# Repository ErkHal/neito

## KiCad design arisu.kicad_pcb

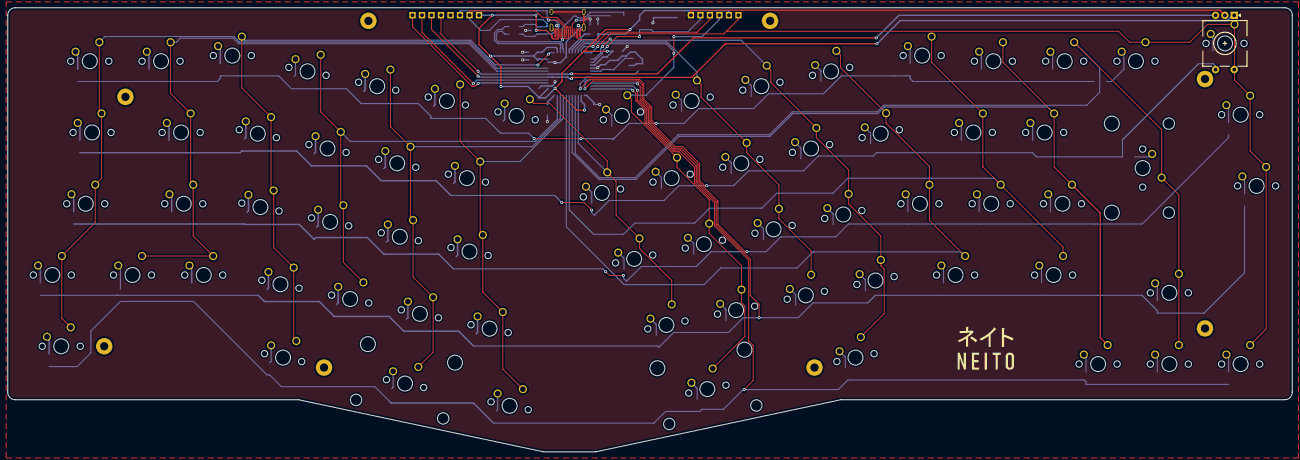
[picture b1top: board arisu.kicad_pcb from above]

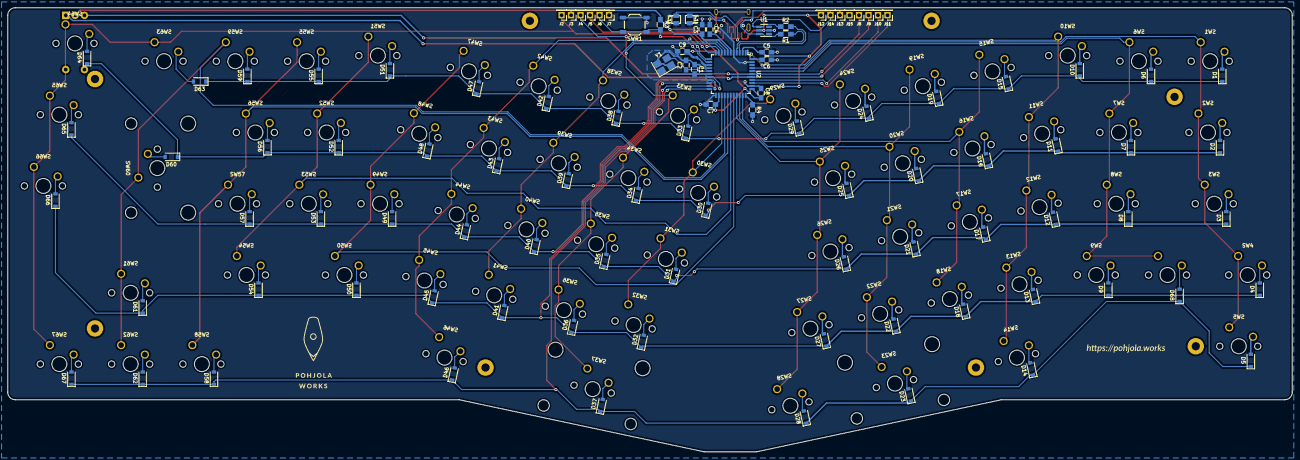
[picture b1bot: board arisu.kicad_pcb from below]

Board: 2 copper layers, 343.4 x 118.7 mm, 179 parts (101 on the bottom side), 106 nets.

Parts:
C1, C2: 22pF; C_0805_HandSoldering
C3: 10uF; C_0805_HandSoldering
C4: 1uF (±10%); C_0805_HandSoldering
C5: 1uF; C_0805_HandSoldering
C6, C7, C8, C9: 0.1uF; C_0805_HandSoldering
D1, D2, D3, D4, D5, D6, D7, D8, D9, D10, D11, D12, D13, D14, D15, D16, D17, D18, D19, D20, D21, D22, D23, D24, D25, D26, D27, D28, D29, D30, D31, D32, D33, D34, D35, D36, D37, D38, D39, D40, D41, D42, D43, D44, D45, D46, D47, D48, D49, D50, D51, D52, D53, D54, D55, D56, D57, D58, D59, D60, D61, D62, D63, D64, D65, D66, D67, D68: D; D_SOD-123
ENC0: Rotary_Encoder_Switch; RotaryEncoder_EC11
H1, H2, H3, H4, H5, H6, H7, H8: MountingHole; MountingHole_2.2mm_M2_Pad
J2: MISO; Pin_Header_Straight_1x01_Pitch2.54mm
J3, J12: VCC; Pin_Header_Straight_1x01_Pitch2.54mm
J4: SCK; Pin_Header_Straight_1x01_Pitch2.54mm
J5: MOSI; Pin_Header_Straight_1x01_Pitch2.54mm
J6: RES; Pin_Header_Straight_1x01_Pitch2.54mm
J7, J15: GND; Pin_Header_Straight_1x01_Pitch2.54mm
J8: PF4; Pin_Header_Straight_1x01_Pitch2.54mm
J9: PF5; Pin_Header_Straight_1x01_Pitch2.54mm
J10: PF6; Pin_Header_Straight_1x01_Pitch2.54mm
J11: PF7; Pin_Header_Straight_1x01_Pitch2.54mm
J13: D+; Pin_Header_Straight_1x01_Pitch2.54mm
J14: D-; Pin_Header_Straight_1x01_Pitch2.54mm
R1, R2: 22; R_0805_HandSoldering
R3, R4: 10K; R_0805_HandSoldering
R_CC1, R_CC2: 5.1k; R_2012
SW1, SW6, SW7, SW8, SW9, SW10, SW11, SW12, SW13, SW15, SW16, SW17, SW18, SW19, SW20, SW21, SW22, SW24, SW25, SW26, SW27, SW28, SW29, SW30, SW31, SW32, SW33, SW34, SW35, SW36, SW38, SW39, SW40, SW41, SW42, SW43, SW44, SW45, SW47, SW48, SW49, SW50, SW51, SW52, SW53, SW55, SW56, SW57, SW58, SW59, SW61, SW62, SW63, SW64, SW65, SW66, SW67: SW_Push; SW_Cherry_MX_1.00u_PCB
SW2, SW5, SW14, SW46: SW_Push; SW_Cherry_MX_1.50u_PCB
SW3, SW54: SW_Push; SW_Cherry_MX_1.75u_PCB
SW4: SW_Push; SW_Cherry_MX_1.25u_PCB
SW23: SW_Push; SW_Cherry_MX_2.00u_PCB_ReversedStabilizers
SW37: SW_Push; SW_Cherry_MX_2.75u_PCB_ReversedStabilizers
SW60: SW_Push; SW_Cherry_MX_2.00u_PCB
SW68: SW_Push; MX_1.00u_PCB
SWR1: SW_Push; SW_SPST_TL3342
U1: USBLC6-2SC6; SOT-23-6_Handsoldering
U2: ATmega32U4-AU; TQFP-44_10x10mm_Pitch0.8mm
USB_C1: USB_C_Receptacle_HRO_TYPE-C-31-M-12; USB_C_Receptacle_HRO_TYPE-C-31-M-12-HandSoldering
Y1: Crystal_GND24; Crystal_SMD_SeikoEpson_FA238-4pin_3.2x2.5mm_HandSoldering

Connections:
/MISO: ENC0.S2, J2.1, SW63.1, SW64.1, SW65.1, SW66.1, SW67.1, U2.11
/MOSI: J5.1, U2.10
/PF4: ENC0.B, J8.1, U2.39
/PF5: ENC0.A, J9.1, U2.38
/PF6: J10.1, U2.37
/PF7: J11.1, U2.36
/SCK: J4.1, SW33.1, SW34.1, SW35.1, SW36.1, SW37.1, U2.9
/col0: SW1.1, SW2.1, SW3.1, SW4.1, SW5.1, U2.41
/col1: SW6.1, SW7.1, SW8.1, SW9.1, SW68.1, U2.40
/col2: SW10.1, SW11.1, SW12.1, SW13.1, SW14.1, U2.1
/col3: SW15.1, SW16.1, SW17.1, SW18.1, U2.32
/col4: SW19.1, SW20.1, SW21.1, SW22.1, SW23.1, U2.31
/col5: SW24.1, SW25.1, SW26.1, SW27.1, SW28.1, U2.30
/col6: SW29.1, SW30.1, SW31.1, SW32.1, U2.25
/col8: SW38.1, SW39.1, SW40.1, SW41.1, U2.8
/col9: SW42.1, SW43.1, SW44.1, SW45.1, SW46.1, U2.12
/col10: SW47.1, SW48.1, SW49.1, SW50.1, U2.29
/col11: SW51.1, SW52.1, SW53.1, SW54.1, U2.28
/col12: SW55.1, SW56.1, SW57.1, SW58.1, U2.27
/col13: SW59.1, SW60.1, SW61.1, SW62.1, U2.26
/row0: D1.1, D6.1, D10.1, D15.1, D19.1, D24.1, D29.1, D33.1, D38.1, D42.1, D47.1, D51.1, D55.1, D59.1, D63.1, U2.18
/row1: D2.1, D7.1, D11.1, D16.1, D20.1, D25.1, D30.1, D34.1, D39.1, D43.1, D48.1, D52.1, D56.1, D60.1, D64.1, ENC0.S1, U2.19
/row2: D3.1, D8.1, D12.1, D17.1, D21.1, D26.1, D31.1, D35.1, D40.1, D44.1, D49.1, D53.1, D57.1, D65.1, U2.20
/row3: D4.1, D9.1, D13.1, D18.1, D22.1, D27.1, D32.1, D36.1, D41.1, D45.1, D50.1, D54.1, D61.1, D66.1, U2.21
/row4: D5.1, D14.1, D23.1, D28.1, D37.1, D46.1, D58.1, D62.1, D67.1, D68.1, U2.22
/~RES~: J6.1, R3.2, SWR1.2, U2.13
D+: R1.1, U2.4
D-: R2.1, U2.3
GND: C1.1, C2.2, C3.2, C4.2, C5.2, C6.2, C7.2, C8.2, C9.2, ENC0.C, J7.1, J15.1, R4.2, R_CC1.1, R_CC2.2, SWR1.1, U1.2, U2.5, U2.15, U2.23, U2.35, U2.43, USB_C1.A1, USB_C1.A12, USB_C1.S1, Y1.2, Y1.4
unnamed: C4.1, U2.6
unnamed: D1.2, SW1.2
unnamed: D2.2, SW2.2
unnamed: D3.2, SW3.2
unnamed: D4.2, SW4.2
unnamed: D5.2, SW5.2
unnamed: D6.2, SW6.2
unnamed: D7.2, SW7.2
unnamed: D8.2, SW8.2
unnamed: D9.2, SW9.2
unnamed: D10.2, SW10.2
unnamed: D11.2, SW11.2
unnamed: D12.2, SW12.2
unnamed: D13.2, SW13.2
unnamed: D14.2, SW14.2
unnamed: D15.2, SW15.2
unnamed: D16.2, SW16.2
unnamed: D17.2, SW17.2
unnamed: D18.2, SW18.2
unnamed: D19.2, SW19.2
unnamed: D20.2, SW20.2
unnamed: D21.2, SW21.2
unnamed: D22.2, SW22.2
unnamed: D23.2, SW23.2
unnamed: D24.2, SW24.2
unnamed: D25.2, SW25.2
unnamed: D26.2, SW26.2
unnamed: D27.2, SW27.2
unnamed: D28.2, SW28.2
unnamed: D29.2, SW29.2
unnamed: D30.2, SW30.2
unnamed: D31.2, SW31.2
unnamed: D32.2, SW32.2
unnamed: D33.2, SW33.2
unnamed: D34.2, SW34.2
unnamed: D35.2, SW35.2
unnamed: D36.2, SW36.2
unnamed: D37.2, SW37.2
unnamed: D38.2, SW38.2
unnamed: D39.2, SW39.2
unnamed: D40.2, SW40.2
unnamed: D41.2, SW41.2
unnamed: D42.2, SW42.2
unnamed: D43.2, SW43.2
unnamed: D44.2, SW44.2
unnamed: D45.2, SW45.2
unnamed: D46.2, SW46.2
unnamed: D47.2, SW47.2
unnamed: D48.2, SW48.2
unnamed: D49.2, SW49.2
unnamed: D50.2, SW50.2
unnamed: D51.2, SW51.2
unnamed: D52.2, SW52.2
unnamed: D53.2, SW53.2
unnamed: D54.2, SW54.2
unnamed: D55.2, SW55.2
unnamed: D56.2, SW56.2
unnamed: D57.2, SW57.2
unnamed: D58.2, SW58.2
unnamed: D59.2, SW59.2
unnamed: D60.2, SW60.2
unnamed: D61.2, SW61.2
unnamed: D62.2, SW62.2
unnamed: D63.2, SW63.2
unnamed: D64.2, SW64.2
unnamed: D65.2, SW65.2
unnamed: D66.2, SW66.2
unnamed: D67.2, SW67.2
unnamed: D68.2, SW68.2
unnamed: J13.1, R1.2, U1.6, USB_C1.A6, USB_C1.B6
unnamed: J14.1, R2.2, U1.4, USB_C1.A7, USB_C1.B7
unnamed: R4.1, U2.33
unnamed: R_CC1.2, USB_C1.A5
unnamed: R_CC2.1, USB_C1.B5
VCC: C3.1, C5.1, C6.1, C7.1, C8.1, C9.1, J3.1, J12.1, R3.1, U1.5, U2.2, U2.7, U2.14, U2.24, U2.34, U2.44, USB_C1.A4, USB_C1.A9
XTAL1: C1.2, U2.17, Y1.1
XTAL2: C2.1, U2.16, Y1.3

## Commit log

2020-08-30 WIP Neito
